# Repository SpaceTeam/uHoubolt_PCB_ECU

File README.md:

# µHoubolt Engine Control Unit (ECU) Hardware

## Features
- 3 RC Servo outputs with position feedback and current measurement
- 2 High-current low side FET outputs with current measurement
- 3 Pyro outputs with high side switch (supplied separately from main supply), continuity check, current measurement and current limiting
- 6 Pressure sensor inputs, individually configurable for 0-150mV differential, 0-5V single ended and 4-20mA
- 3 Temperature sensor inputs for resistive types
- Status LEDs on all outputs, voltage rails and two user programmable
- 2 CAN-FD buses, multiple connectors per bus for simple daisy-chaining
- Debug interface with SWD and UART
- 70x40mm 4-layer PCB, additional power and CAN connectors on back side

## Known Issues
- Wrong Footprint for STM
- Igniter continuity check not working without Pyro voltage
- Missing low pass filter for servo current measurement
- Switching on the 12V supply (or power cycling it) when the pyro supply is already active can initiate igniters (poblematic in combination with issue in PMU, see PMU Known Issues and EuRoC flight report). Pull down resistors on igniter enable lines are missing.
- Using current sense amps for the pressure sensor inputs is bad, their low input impedance significantly reduces the measured values. Wasn't a problem (and wasn't even noticed?) as the measurements are still linear (tested by GATE) and the sensors were calibrated against a Baluff sensor, but should be avoided in future revisions by using instrumentation amplifiers (e.g. INA350).

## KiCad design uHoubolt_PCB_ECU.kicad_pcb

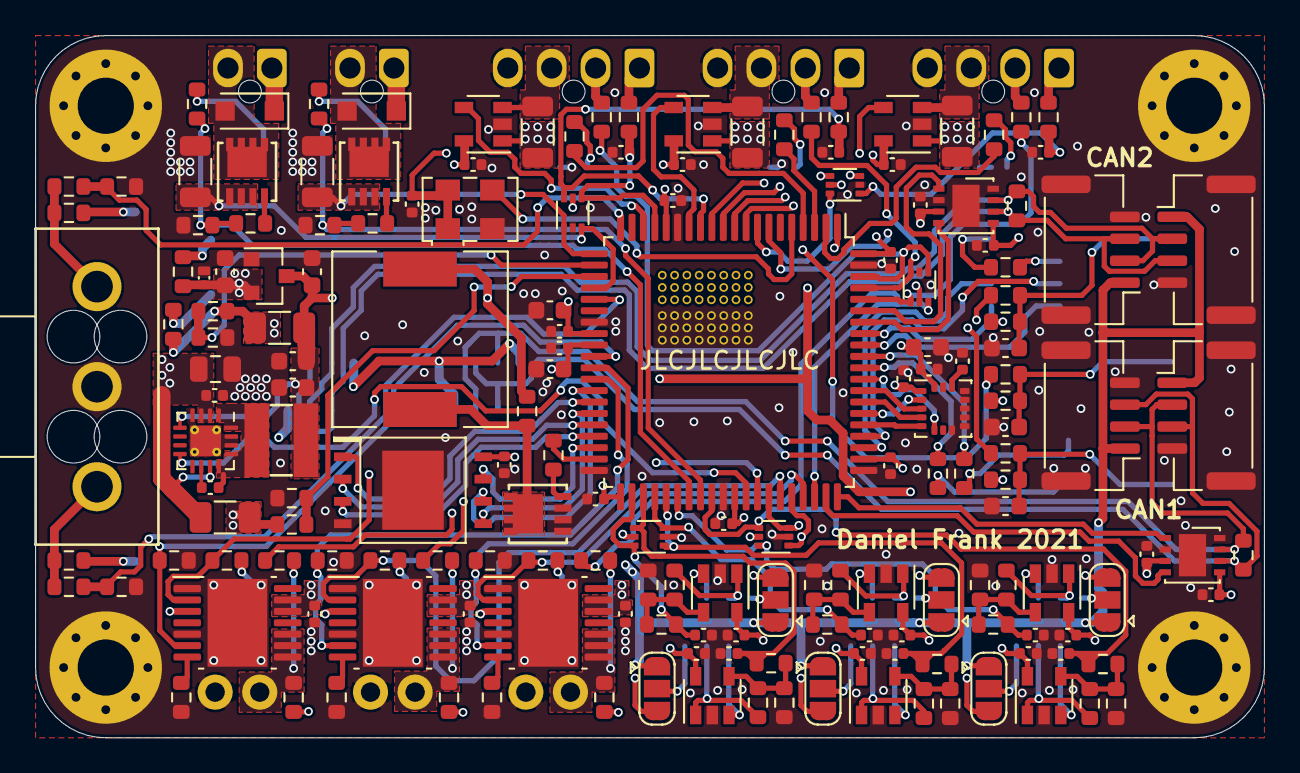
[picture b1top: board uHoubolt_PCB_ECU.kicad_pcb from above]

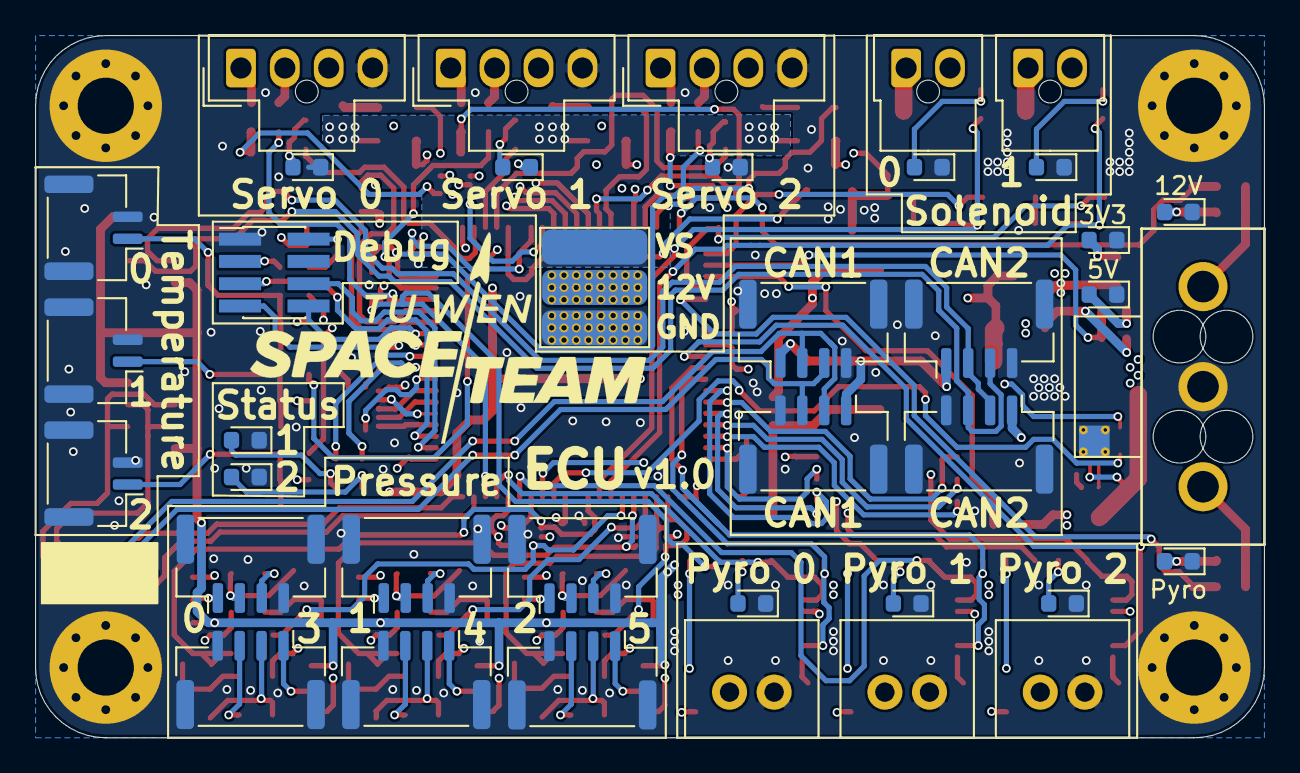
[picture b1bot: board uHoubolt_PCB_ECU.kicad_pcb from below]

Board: 4 copper layers, 70.0 x 40.0 mm, 216 parts (38 on the bottom side), 140 nets.

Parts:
C1, C2, C12, C17, C21, C22, C23, C24, C25, C26, C27, C30, C31, C32, C33, C34, C35, C37, C38, C39, C40, C41, C43, C44, C45, C46, C47, C48, C49, C50, C51, C52, C53, C56, C57, C58, C59, C60, C61: 100n; C_0402_1005Metric
C10: 10µ; C_0805_2012Metric
C16, C20, C28, C29, C36: 2µ2; C_0603_1608Metric
C18, C19, C42, C54, C55: 22µ; C_0603_1608Metric
D1: VIN; LED_0603_1608Metric
D2: PYRO; LED_0603_1608Metric
D3: 5V; LED_0603_1608Metric
D4: LED 1; LED_0603_1608Metric
D5: LED 2; LED_0603_1608Metric
D6, D9: OUT 1; LED_0603_1608Metric
D7, D10: Shottky; D_SOD-123F
D8, D11, D12: PYRO 1; LED_0603_1608Metric
D13: TVS 3V3; SOD882D
D14, D15, D16: Servo; LED_0603_1608Metric
D17: 3V3; LED_0603_1608Metric
F1, F2: 350mA; Fuse_1206_3216Metric
G1: SpaceTeam_LOGO; ST_Logo_new
H1, H2, H3, H4: MH; MountingHole_3.2mm_M3_Pad_Via
J1: Power In; Molex_MegaFit_1x03_Vertical_Doublesided
J2: Debug; PinHeader_2x04_P1.27mm_Vertical_SMD
J3, J5, J35, J37: CAN1; JST_GH_BM04B-GHS-TBT_1x04-1MP_P1.25mm_Vertical
J4, J6, J36, J38: CAN2; JST_GH_BM04B-GHS-TBT_1x04-1MP_P1.25mm_Vertical
J7, J12, J13, J14, J15, J23: Pressure; JST_GH_BM04B-GHS-TBT_1x04-1MP_P1.25mm_Vertical
J8, J16, J17: TEMP; JST_GH_BM02B-GHS-TBT_1x02-1MP_P1.25mm_Vertical
J9, J18, J19: Servo; Molex_Nano-Fit_105309-xx04_1x04_P2.50mm_Vertical
J10, J20: Solenoid; Molex_Nano-Fit_105309-xx02_1x02_P2.50mm_Vertical
J11, J21, J22: Pyro; Molex_SL_1x2_Vertical
JP1, JP3, JP4, JP5, JP6, JP7: V_SEL; SolderJumper-3_P1.3mm_Open_RoundedPad1.0x1.5mm
JP2: Servo Voltage Select; Jumper3_6x2mm_Vias23
L2: 4µ7; SRN4018TA-4R7M
LS1: Speaker; Piezo_Buzzer
Q1, Q2, Q3: SISA88DN or similar; PowerPAK_1212-8
R1, R21, R37, R40, R43, R46: 5k6/0; R_0603_1608Metric
R2, R22, R38, R41, R44, R47: 10k/160; R_0603_1608Metric
R3, R6, R24, R27, R35, R49, R50, R53, R56, R64, R69, R75, R76, R78: 1k; R_0603_1608Metric
R4, R8, R12, R33, R34, R36, R62, R63, R65, R67, R68, R70: 56k; R_0603_1608Metric
R5, R7, R9, R13, R14, R15, R16, R23, R25, R29, R39, R42, R45, R48, R51, R54, R58, R71, R72, R73: 10k; R_0603_1608Metric
R10, R11, R17, R18, R19, R20, R28, R30, R32, R57, R59, R61, R66, R74, R77: 120; R_0603_1608Metric
R26, R31, R52, R55, R60: 10m 1W; R_1206_3216Metric
U1, U9, U10, U12, U13, U14, U15, U16, U17: INA180B1; SOT-23-5
U2: TS30041-M050QFNR; QFN-16-1EP_3x3mm_P0.5mm_EP1.75x1.75mm_ThermalVias
U3: MCP1700-3302E; SOT-23
U4, U5: MCP2562FDx-x_MF; DFN-8-1EP_3x3mm_P0.65mm_EP1.55x2.4mm
U6: STM32G491MET6-LQFP80; LQFP-80_14x14mm_P0.65mm
U7: ICM-20602; LGA-16_3x3mm_P0.5mm_LayoutBorder3x5y
U8: W25Q256JV; WSON-8-8x6mm
U11, U18, U19: TPS1HC100; HTSSOP-14-1EP_4.4x5mm_P0.65mm_EP3.4x5mm_Mask3x3.1mm
U20, U21, U22, U23, U24: D1213A-04V; SOT-563
X1: TXC-7C; Oscillator_SMD_TXC_7C-4Pin_5.0x3.2mm

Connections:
+3V3: C1.1, C20.2, C21.1, C22.1, C23.1, C24.1, C25.2, C28.2, C29.2, C30.2, C31.2, C32.2, C33.2, C34.2, C35.2, C36.1, C37.1, C38.1, C39.2, C44.1, C46.1, C48.1, C50.1, C52.1, C57.1, C59.1, D13.1, J2.2, R16.2, R24.1, R34.2, R49.1, R50.1, R63.2, R68.2, R76.1, U1.5, U3.2, U4.5, U5.5, U6.1, U6.16, U6.28, U6.29, U6.41, U6.51, U6.62, U6.80, U7.1, U7.16, U8.8, U9.5, U10.5, U11.3, U12.5, U13.5, U14.5, U15.5, U16.5, U17.5, U18.3, U19.3, U20.5, U21.5, U22.5, U23.5, U24.5, X1.1, X1.4
+5V: F1.1, J3.1, J4.1, J5.1, J6.1, J35.1, J36.1, J37.1, J38.1, JP1.1, JP3.1, JP4.1, JP5.1, JP6.1, JP7.1, R14.1, R75.1
+12V: C10.1, C12.1, D7.1, D10.1, F2.2, J1.1, J10.1, J20.1, JP2.2, LS1.1, R3.1, R4.1, R78.1, U2.2, U2.3, U2.11
+12VA: F2.1, JP1.3, JP3.3, JP4.3, JP5.3, JP6.3, JP7.3, R12.1
/5V_PGOOD: U2.8, U6.52
/5V_SENSE: R14.2, R15.1, U6.22
/5V_unfused: C16.2, C18.1, C19.1, C26.1, C27.1, F1.2, L2.2, U2.5, U3.3, U4.3, U5.3
/12VA_SENSE: R12.2, R13.1, U6.23
/12V_SENSE: R4.2, R5.1, U6.20
/CAN1_H: J3.2, J5.2, J35.2, J37.2, R17.1, U4.7
/CAN1_L: J3.3, J5.3, J35.3, J37.3, R17.2, U4.6
/CAN1_RX: U4.4, U6.59
/CAN1_TX: U4.1, U6.60
/CAN2_H: J4.2, J6.2, J36.2, J38.2, R18.1, U5.7
/CAN2_L: J4.3, J6.3, J36.3, J38.3, R18.2, U5.6
/CAN2_RX: U5.4, U6.74
/CAN2_TX: U5.1, U6.75
/CLK: U6.5, X1.3
/IMU_INT: U6.69, U7.6
/LED_1: R19.2, U6.71
/LED_2: R20.2, U6.70
/NRST: J2.3, R16.1, U6.7
/PRESS_0: C41.1, R23.2, U6.46, U23.6
/PRESS_1: C53.1, R48.2, U6.44, U24.3
/PRESS_2: C2.1, R7.2, U6.42, U24.6
/PRESS_3: C51.1, R45.2, U6.49, U23.4
/PRESS_4: C49.1, R42.2, U6.45, U24.1
/PRESS_5: C47.1, R39.2, U6.43, U24.4
/PYRO_0_CONT: R36.1, U6.58, U22.6
/PYRO_0_CTRL: R32.1, U6.57, U11.2
/PYRO_0_CURR: R35.2, U6.32, U11.6
/PYRO_1_CONT: R65.1, U6.56, U23.1
/PYRO_1_CTRL: R61.1, U6.55, U18.2
/PYRO_1_CURR: R64.2, U6.31, U18.6
/PYRO_2_CONT: R70.1, U6.54, U23.3
/PYRO_2_CTRL: R66.1, U6.53, U19.2
/PYRO_2_CURR: R69.2, U6.30, U19.6
/PYRO_SENSE: R8.2, R9.1, U6.25
/QSPI1_BK1_IO0: U6.35, U8.5
/QSPI1_BK1_IO1: U6.36, U8.2
/QSPI1_BK1_IO2: U6.37, U8.3
/QSPI1_BK1_IO3: U6.38, U8.7
/QSPI1_BK1_NCS: U6.34, U8.1
/QSPI1_CLK: U6.33, U8.6
/SERVO_0_CURR: U6.12, U10.4
/SERVO_0_FDBK: C43.1, R25.1, U6.11, U21.1
/SERVO_0_LED: R10.1, U6.2
/SERVO_0_PWM: R27.1, U6.76, U22.4
/SERVO_1_CURR: U6.14, U17.4
/SERVO_1_FDBK: C58.1, R54.1, U6.13, U20.6
/SERVO_1_LED: R74.1, U6.3
/SERVO_1_PWM: R56.1, U6.77, U22.3
/SERVO_2_CURR: U6.18, U16.4
/SERVO_2_FDBK: C56.1, R51.1, U6.17, U20.4
/SERVO_2_LED: R11.1, U6.4
/SERVO_2_PWM: R53.1, U6.78, U22.1
/SOLENOID_0_CTRL: R57.1, R58.2, R59.1, U6.48
/SOLENOID_0_CURR: Q2.3, R60.1, U6.21, U20.1
/SOLENOID_1_CTRL: R28.1, R29.2, R30.1, U6.47
/SOLENOID_1_CURR: Q1.3, R31.1, U6.24, U20.3
/SPI_IMU_CS: U6.65, U7.5
/SPI_MISO: U6.67, U7.4
/SPI_MOSI: U6.68, U7.3
/SPI_SCK: U6.66, U7.2
/SWCLK: J2.5, U6.64
/SWDIO: J2.6, U6.63
/Speaker: R77.1, U6.39
/TEMP_0: R73.1, U6.8, U21.6
/TEMP_1: R71.1, U6.9, U21.4
/TEMP_2: R72.1, U6.10, U21.3
/UART_RX: J2.8, U6.73
/UART_TX: J2.7, U6.72
GND: C1.2, C2.2, C10.2, C12.2, C16.1, C18.2, C19.2, C20.1, C21.2, C22.2, C23.2, C24.2, C25.1, C26.2, C27.2, C28.1, C29.1, C30.1, C31.1, C32.1, C33.1, C34.1, C35.1, C36.2, C37.2, C38.2, C39.1, C40.1, C41.2, C42.1, C43.2, C44.2, C45.2, C46.2, C47.2, C48.2, C49.2, C50.2, C51.2, C52.2, C53.2, C54.1, C55.1, C56.2, C57.2, C58.2, C59.2, C60.2, C61.2, D1.1, D2.1, D3.1, D4.1, D5.1, D6.1, D8.1, D9.1, D11.1, D12.1, D13.2, D14.1, D15.1, D16.1, D17.1, H1.1, H2.1, H3.1, H4.1, J1.2, J2.1, J3.4, J3.MP, J4.4, J4.MP, J5.4, J5.MP, J6.4, J6.MP, J7.4, J7.MP, J8.2, J8.MP, J9.4, J11.1, J12.4, J12.MP, J13.4, J13.MP, J14.4, J14.MP, J15.4, J15.MP, J16.2, J16.MP, J17.2, J17.MP, J18.4, J19.4, J21.1, J22.1, J23.4, J23.MP, J35.4, J35.MP, J36.4, J36.MP, J37.4, J37.MP, J38.4, J38.MP, JP2.3, Q3.3, R2.2, R5.2, R9.2, R13.2, R15.2, R22.2, R29.1, R31.2, R33.1, R35.1, R38.2, R41.2, R44.2, R47.2, R58.1, R60.2, R62.1, R64.1, R67.1, R69.1, U1.2, U2.4, U2.14, U2.15, U2.17, U3.1, U4.2, U4.8, U4.9, U5.2, U5.8, U5.9, U6.15, U6.27, U6.40, U6.50, U6.61, U6.79, U7.8, U7.9, U7.10, U7.11, U7.12, U7.13, U7.15, U8.4, U8.9, U9.2, U10.2, U11.1, U11.5, U11.15, U12.2, U13.2, U14.2, U15.2, U16.2, U17.2, U18.1, U18.5, U18.15, U19.1, U19.5, U19.15, U20.2, U21.2, U22.2, U23.2, U24.2, X1.2
unnamed: C17.1, U2.10
unnamed: C17.2, L2.1, U2.1, U2.12, U2.13, U2.16
unnamed: C40.2, U7.14
unnamed: C42.2, J8.1, R24.2, R71.2
unnamed: C54.2, J16.1, R49.2, R72.2
unnamed: C55.2, J17.1, R50.2, R73.2
unnamed: D1.2, R3.2
unnamed: D2.2, R6.2
unnamed: D3.2, R75.2
unnamed: D4.2, R19.1
unnamed: D5.2, R20.1
unnamed: D6.2, R28.2
unnamed: D7.2, J10.2, Q1.2
unnamed: D8.2, R32.2
unnamed: D9.2, R57.2
unnamed: D10.2, J20.2, Q2.2
unnamed: D11.2, R61.2
unnamed: D12.2, R66.2
unnamed: D14.2, R10.2
unnamed: D15.2, R11.2
unnamed: D16.2, R74.2
unnamed: D17.2, R76.2
unnamed: J7.1, JP1.2
unnamed: J7.2, R21.1, U9.1
unnamed: J7.3, U9.3
unnamed: J9.1, R25.2
unnamed: J9.2, R27.2
unnamed: J9.3, R26.1, U10.3
unnamed: J11.2, R34.1, R36.2, U11.8, U11.9, U11.10
unnamed: J12.1, JP4.2
unnamed: J12.2, R37.1, U12.1
unnamed: J12.3, U12.3
unnamed: J13.1, JP5.2
unnamed: J13.2, R40.1, U13.1
unnamed: J13.3, U13.3
unnamed: J14.1, JP6.2
unnamed: J14.2, R43.1, U14.1
unnamed: J14.3, U14.3
unnamed: J15.1, JP7.2
unnamed: J15.2, R46.1, U15.1
unnamed: J15.3, U15.3
unnamed: J18.1, R51.2
unnamed: J18.2, R53.2
unnamed: J18.3, R52.1, U16.3
unnamed: J19.1, R54.2
unnamed: J19.2, R56.2
unnamed: J19.3, R55.1, U17.3
unnamed: J21.2, R63.1, R65.2, U18.8, U18.9, U18.10
unnamed: J22.2, R68.1, R70.2, U19.8, U19.9, U19.10
unnamed: J23.1, JP3.2
unnamed: J23.2, R1.1, U1.1
unnamed: J23.3, U1.3
unnamed: LS1.2, Q3.2, R78.2
unnamed: Q1.1, R30.2
unnamed: Q2.1, R59.2
unnamed: Q3.1, R77.2
unnamed: R1.2, R2.1, R7.1, U1.4
unnamed: R21.2, R22.1, R23.1, U9.4
unnamed: R33.2, U11.7
unnamed: R37.2, R38.1, R39.1, U12.4
unnamed: R40.2, R41.1, R42.1, U13.4
unnamed: R43.2, R44.1, R45.1, U14.4
unnamed: R46.2, R47.1, R48.1, U15.4
unnamed: R62.2, U18.7
unnamed: R67.2, U19.7
PYRO: C45.1, C60.1, C61.1, J1.3, R6.1, R8.1, U11.12, U11.13, U18.12, U18.13, U19.12, U19.13
VS: JP2.1, R26.2, R52.2, R55.2, U10.1, U16.1, U17.1

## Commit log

2020-11-16 add submodule
2020-11-16 create kicad project with library paths
2020-11-17 fix library path
2020-11-19 update TXV_LIB
2020-12-03 add mcu schematic
2020-12-03 new main version
2020-12-17 add power symbols
2021-02-25 add 10A solenoid circuit
2021-02-25 add 5V Zünder circuit
2021-02-25 add continuity sense to 5V Zünder circuit
2021-04-12 add 2x variable input pressure sensor circuit
2021-05-08 Added modules from Trello list. Todo: Review, assign pins to labels, component naming.
2021-05-08 Resolved TXV lib commit conflict, no changes
2021-05-30 Changed IMU and assigned sigs to uC pins.
2021-08-11 Implemented changes after design review
2021-11-05 cleanup of file structure
2021-11-10 schematic mostly done
2021-11-16 schematic even more done
2021-11-16 moved I/O to subsheets, started layout
2021-11-17 preliminary placement done
2021-11-17 small changes, added Step File
2021-11-18 changed form factor to better fit into uHb engine section
2021-12-01 moved 7V4 buck to separate board
2021-12-14 many small changes, before removing servo buck converter
2021-12-14 placement almost done
2021-12-14 fixed net names
2021-12-15 schematic done, preliminary placement done
2021-12-15 routing started
2021-12-19 routing done, drc clean (3 errors to be ignored)
2021-12-19 small improvements, updated doc
2021-12-19 small changes, generated gerbers
2021-12-22 some more small changes
2021-12-22 tiny changes, version to be ordered
2022-01-01 updated to KiCad v6
2022-01-12 WIP v1.1, fixed JP2 footprint, replaced STM footprint, re-routing in progress
2023-01-22 Add license
